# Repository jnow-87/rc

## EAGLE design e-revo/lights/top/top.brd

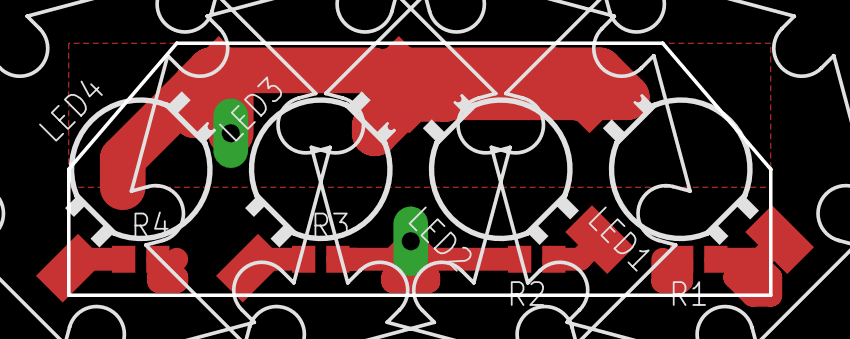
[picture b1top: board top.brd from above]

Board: 2 copper layers, 39.0 x 14.0 mm, 10 parts (0 on the bottom side), 6 nets.

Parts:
LED1, LED2, LED3, LED4: Z-POWER-LED; Z-POWER-LED-PCB-TYPE
R1, R2, R3, R4: 12; R0805
U$1, U$2: PAD

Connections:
+5V: R1.2, R2.2, R3.2, R4.2, U$2.P$1
GND: LED1.C, LED2.C, LED3.C, LED4.C, U$1.P$1
unnamed: LED4.A, R4.1
unnamed: LED3.A, R3.1
unnamed: LED2.A, R2.1
unnamed: LED1.A, R1.1

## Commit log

2022-08-17 [initial]
2022-08-17 [body-clips: front, back]
    Add body clip designs for front and back.
2022-08-17 [slicer configs: initial]
    Initial snapmaker and curo configurations.
2022-08-17 [light: top]
    Add design and pcb for the top led bar.
2022-08-17 [body-clips: battery]
    Add a design for the battery cable clip.
2022-08-20 [front-tools: clip, holder, shovel]
    Add a front shovel with clip and holder to attach it to the body.
2022-12-31 [light: mill config]
    Update the milling configuration, replacing milldrill with drill only
    and updating some heights and speeds.
2023-05-21 [battery: adjust top join]
    Move the top join towards the center to make the cable easier to grab.
2023-07-19 [body-clips: alternate sizes]
    Add a long version of the back and a short one of the front body clips.
2023-07-19 [lights: solder mask export]
    Add a build target to export a solder mask image.
2023-08-15 [e-revo: restructure]
    Move all e-revo projects into a separate folder.
2023-08-27 [trx-4m: initial]
    Add trx-4m body clips and shock tower parts.
